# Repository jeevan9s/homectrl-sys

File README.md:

# homectrl

Home-automation controller with a Next.js dashboard. 

 ### Status
>- Controller PCB currently being manufactures
>- Firmware and **docs development** in progress.
>- Mechanical components currently being printed.

<details>
<summary><strong>Table of Contents</strong></summary>

- [homectrl](#homectrl)
    - [Status](#status)
  - [Overview](#overview)
  - [Features](#features)
    - [Controller](#controller)
    - [App](#app)
    - [Mechanical](#mechanical)
  - [Architecture](#architecture)
    - [Systems](#systems)
  - [Electrical](#electrical)
    - [Power System](#power-system)
    - [Microcontroller](#microcontroller)
    - [Pump Interface](#pump-interface)
    - [Stepper Motor Interface](#stepper-motor-interface)
    - [Peripheral Devices](#peripheral-devices)
  - [Mechanical](#mechanical-1)
    - [Container](#container)
    - [Lid](#lid)
  - [Firmware](#firmware)
  - [Web-App](#web-app)
  - [Repository Structure](#repository-structure)
  - [Gallery](#gallery)

</details>

I built homectrl because I wanted to automate my first apartment. 

<table> 
  <tr> 
    <td width="50%"> 
       
    </td> 
    <td width="50%"> 
       
    </td> 
  </tr> 
</table>

## Overview
Practicality is a consistent motive when building. 

As I moved into my first apartment during my first year at Queen's University, I wanted a device capable of smart-control for plants and window blinds, which are main components of my studio. This pushed me to build **homectrl**, a controller that leverages sensor readings, actuators, and WiFi for home automation. 

The first version was manufactured in October of 2025, and this was my first PCB designed. It was a bit elementary, lots of breakout boards soldered on, an MCU devkit, etc. 
Over the year I designed several other PCBs and learned a lot, which pushed me to produce a second version that I can use reliably for my 2nd year in Kingston. 

It's now June and the controller is being manufactured while I write docs and firmware. 

## Features 
### Controller

The controller is powered by a 12V 2A adapter and driven by an ESP32-S3.

Below is a list of features from power circuits to various peripherals. 
- Power-entry circuitry with OC/OV protetction, RPP, and PI-filter
- Regulation circuit featuring buck converter, 5V ORing, and LDO for logic power (3V3) 
- ESP32-S3 breakout circuitry with USB differential routing, S3 boot mode selection and reset toggle. 
- Controlled power delivery via CMOS and PMOS for main pump and moisture sensor power. 
- Low-side switching for pump control. 
- Stepper motor driven by TMC2209 with UART for blind control. 
- Float switches for monitoring irrigation tank. 
- Analog soil moisture sensor connectors with local RC filters. 
- ESD protection with TVS diode arrays on all external connections. 
- Visual and audible indication. 

### App

The controller communicates to a Next.js webapp via Websockets and is also connected to Alexa via SinricPro for voice control, over WiFi/MQTT.

- Next.js dashboard with modern responsive shadCN-tailwindcss UI. 
- Slider and switch control via UI. 
- Voice control with Alexa via SinricPro

### Mechanical 
- Lightweight container with USB and power ports and slots for cable management.
- Vents for airflow and audible indication. 
- Magnetic joints for easy lid removal and secure operation. 

## Architecture 
### Systems 

## Electrical 

This section provides low-level explanations of the significant circuits of each "module" of the controller.

I encourage you to clone the repo or you use [KiCanvas](https://kicanvas.org/) to look at the schematic and board files. 

All electronics were designed with **KiCad**.

### Power System

**Power Entry**

The 12V 2A power enters through a barrel jack connector, where it is then met with a 24V 3A fuse for over-current protection. A PTC resettable fuse was selected for durability. 

The positive plug line `VPLUG` is then protected from voltage spikes with a Transient Voltage Supression (TVS) diode placed in paralell for clamping. 
- The diode's standoff @ `14V`
- Breakdown @ `15.3V`
- Clamps @ `23.2V`

The positive line then goes through a Reverse Polarity Protection (RPP) circuit, using a P-Channel MOSFET for lossless efficiency (lower V drop than standard diodes). 

A Zener diode and resistor is placed between the MOSFET's gate and source for gate over-voltage protection. 

A bulk electrolytic (100μF) capacitor, ferrite bead, and high-frequency (0.1μF) capacitor are then placed to create a third-order low pass filter (π-filter). 
- This is used to smooth voltage spikes and reduce EMI.

The ferrite bead was primariy selected for its saturation current and DCR. 

The approximate current draw with safety margin $I_{net}$ is 2A.

$I_{\mathrm{sat}} = 1.5 \times I_{\mathrm{net}} \approx 3 A$

Minimize heat dissipation. 

$DCR$ is 20Ω

$P_{heat} = DCR \times I_{\mathrm{sat}} \approx 0.06 W$

**Voltage Regulation (I)**

The controller uses a cascade regulation system, starting with the `TPS5405DR` buck converter. 

The input voltage is `VPLUG` (12V), after the protection and filtering circuitry, and the output is 5V. 

The $R_{osc}$ value will determine the switching frequency of the converter. 

Switching frequency is governed by the relationship. 
$$R_{\text{OSC}} (\text{k}\Omega) = 21.82 \cdot f_{\text{SW}}^{-1.167}$$

I chose a value of `50kΩ` for a $f_{SW}$ of approximately `525 kHz`

For the soft-start capacitor $C_{ss}$ , I chose a value of `10nF` for a soft-start time of `5ms`

The values below were taken from the [TPS5405DR Datasheet](https://www.ti.com/lit/gpn/tps5405)

$$
C_{SS} = \frac{t_{SS} \cdot I_{SS}}{V_{REF}}
$$

$$
C_{SS} = \frac{(5\,\mathrm{ms})(2\,\mathrm{\mu A})}{0.8\,\mathrm{V}}
= 12.5\,\mathrm{nF}
\approx 10\,\mathrm{nF}
$$

The inductor values were chosen using the equation below. 

$$
L=\frac{V_{out}\left(V_{in}-V_{out}\right)}
{V_{in}f_{sw}\Delta I_L}
$$

Using our calculated $f_{sw}$ from above and our voltage requirements (12V in, 5V out):
$$
L=
\frac{(5\,\mathrm{V})(12\,\mathrm{V}-5\,\mathrm{V})}
{(12\,\mathrm{V})(490\,\mathrm{kHz})(0.6\,\mathrm{A})}

\approx
10\,\mathrm{\mu H}
$$

The Schottky diode is rated for the `2A` output current and `12V`

**5V ORing**

The `5V` rails from both USB and the buck converter are combined using an OR-ing circuit (Dual Ideal Diodes) to prevent backfeeding before feeding the second stage of regulation.

In this configuration, the outputs of both `LM66100` ideal diode controllers are tied together to form the shared `5V` rail. The `CE` pins of each device are also tied to the output rail, ensuring both controllers are only enabled once the rail is present 

This allows for testing over serial with devices that are powered by `VPLUG` (12V). 

**Voltage Regulation (II)**

The second stage of voltage regulation involes a Low-Dropout Regulator (LDO), the `MCP1826S`

It is fed the combined `5V` rail from the OR-ing circuit to produce the controller's logic-level voltage: `3V3`

**Controlled Pump Power Delivery**

The power for the pumps is controlled using a complementary-MOSFET (CMOS) setup, driven by a digital `HIGH` from the S3.

- When the control signal is low or floating, the N-channel MOSFET remains off and a pull-up resistor holds the gate of the P-channel MOSFET at the supply voltage, keeping it disabled and disconnecting the load rail.
- When the control signal is driven high, the N-channel MOSFET turns on and pulls the P-channel gate low, creating sufficient gate-source voltage to enable conduction and connect the supply to the load.

**Voltage Sensing**

A resistor divider circuit is used to produce a signal to be read by the S3's internal ADC.

- $R_1 = 100\,\mathrm{k\Omega}$
- $V_{plug} = 12\,\mathrm{V}$
- $V_{out} = 2\,\mathrm{V}$

$$
R_2 = \frac{R_1 \cdot V_{out}}{V_{batt} - V_{out}}
$$

$$
R_2 = \frac{100\,000 \cdot 2}{12 - 2}
= 20\,\mathrm{k\Omega}
$$

### Microcontroller
The controller is driven by an ESP32-S3-WROOM microcontroller.

**Digital IO**

**Mode Select and Reset Toggle**

The S3 can be put into **BOOT** mode and **RESET** with onboard buttons.

**BOOT** mode determines whether the chip runs existing code from flash memory or waits to download new firmware.
- The ESP32 samples the **BOOT** pin (`GPIO0`) during reset to determine the boot mode.
- It is **active-low**: when pulled to **GND** during reset, the chip enters UART bootloader mode for flashing firmware.
- The circuit uses a momentary push-button to **GND** and a `10kΩ` pull-up resistor to ensure a defined high state during normal operation.

| BOOT0 Level | Boot Mode |
|-------------|-----------|
| HIGH | Programming Mode |
| LOW | Memory Mode |

**RESET** controls the Enable (EN) pin which is the ON/OFF (reset) switch for the ESP32.
- It is **active-low**: when pulled to **GND** it turns off the chip, and when released, it restarts.
- The circuit consists of a momentary push-button, a pull-up resistor to ensure the chip is enabled by default, and a `1µF` capacitor to filter out button noise.

### Pump Interface

<table><tr><td width="50%"></td><td width="50%"></td></tr></table>

The controller interfaces with 12V 300mA rated pumps for irrigation. 

These pumps connect via JST-XH vertical headers and are met with flyback diodes for inductive spike protection, and decoupling to filter out noise. 

Each pump is controlled by a low-side switch using an `A03400A` N-channel MOSFET. 
- The gate of the MOSFET is driven by an S3 GPIO pin and is pulled down to GND for state definition. 
- The drain is connected to the negative terminal of the pump and the source to GND. 

This will bridge the negative pump terminal to GND and effectively turn it `ON` when the gate is `HIGH`. 

### Stepper Motor Interface

The controller interfaces with a `NEMA 17` stepper motor through a `TMC2209` driver for blind control. 

The `NEMA 17` stepper motor connects via a vertical 4-position JST-XH header. 

The positive and negative terminals of both stepper coils feed the OBX and OAX pins of the driver. 

The driver is powered by `VPLUG` and is decoupled for bulk and high-frequency noise with electrolytic and ceramic capacitors. 
- The driver is put to sleep by the `ENN` pin to avoid power consumption, which is why I didn't use a CMOS/controlled-power delivery setup.

The main control signals are `STEP` and `DIR`, controlling the speed and direction, respectively. These connect digital pins on the S3. 

The single-wire UART interface was used for advanced chip config, live diagnostics, and features. 

The `BRA` and `BRB` connect to `0.11Ω` sense resistors to monitor and regulate current through the motor coils. 

For addressing, the `MS1_AD01` and `MS2_AD1` pins are pulled low to set the binary address bits to `00` and the UART slave address to `%0`. 

The `CP0` and `CP1` pins are tied together with a 22nF capacitor to generate a boost voltage for the internal charge pump. This boosted voltage switches the internal N-channel MOSFETs fully on. 

### Peripheral Devices

**Sensors**

The controller interfaces with two capactive soil-moisture sensors (SMS) and an Ambient Light Sensor (ALS). 

These connections are made with vertical 4-pin JST-XH headers. 

I designed the ALS breakout board, in the future I'd be interested in designing the moisture sensors. For now I'm using the Adafruit models.

The `3V3` SMS power  is controlled through a simple `A03407A` P-channel mosfet, and the signals are filtered with a resistor-capacitor network at the S3 ADC pins. 

The ALS communicates with the `I2C` protocol and is powered by `3V3`. 

The two analog signals and I2C clock and data signals are ESD-protected by a `TPD43001` TVS diode array.

**Float Switches**

The controller interfaces with two float switches. 

These connections are made with a vertical 3-pin JST-XH header. 

The signals are pulled up to 3V3 to establish a defined logic stateand filtered with a resistor-capacitor network at the S3 ADC pins. 

**Indicator Components**
- RGB LED
- Passive LEDs for simple indication
- Buzzer for audible indication

## Mechanical 
This section provides insight on the mechanical components of homectrl. 

I used Fusion360 to design everything.   

### Container

The container uses a rounded-rectangular exterior to house the board. 

The board is mounted using M2 standoffs designed from the base of the container. 

- It features USB-C and barrel-jack portholes for easy flashing and power connection.
- The backside has slot cutouts for actuator and sensor cables. 
- Vent holes were used throughout the container for airflow and weight management (more lightweight).

### Lid 

The lid is mounted magnetically on the outer top face of the container using projected holes for small magnets. 
- Its design is honestly quite minimal, I did add a small hole for the controller's RGB LED to shine through. 

## Firmware

## Web-App

## Repository Structure 

## Gallery 

---
**huge thanks to PCBWay for sponsoring this project's first revision.**<br>
[check out **REV A**](https://github.com/jeevan9s/homectrl-sys/tree/rev-A)

---
Jeevan Sanchez, 2026

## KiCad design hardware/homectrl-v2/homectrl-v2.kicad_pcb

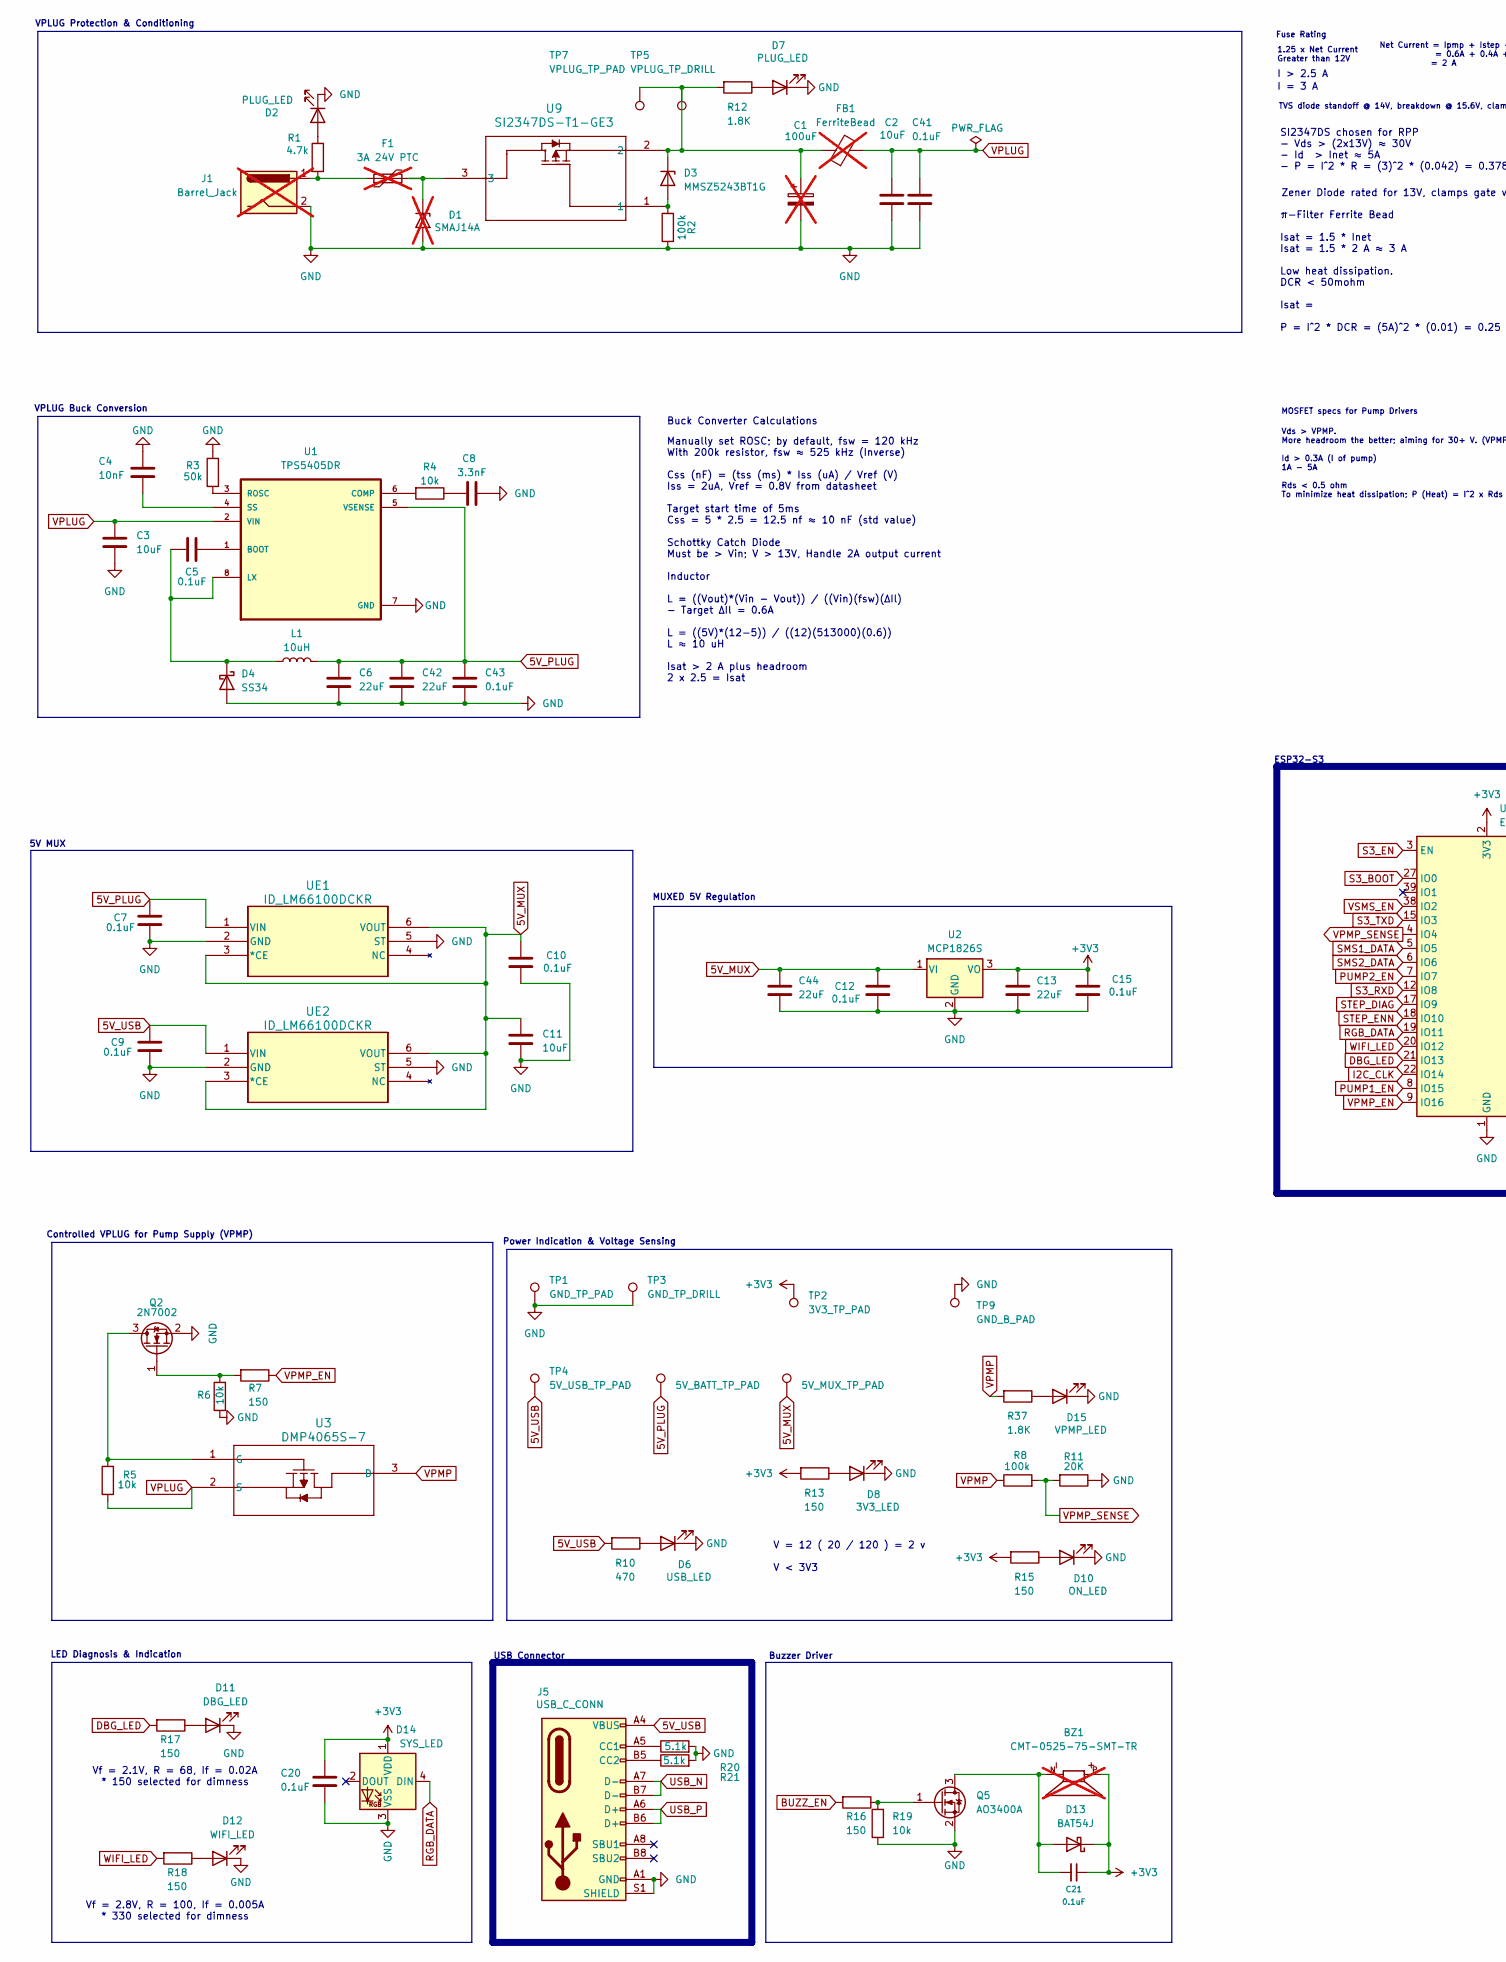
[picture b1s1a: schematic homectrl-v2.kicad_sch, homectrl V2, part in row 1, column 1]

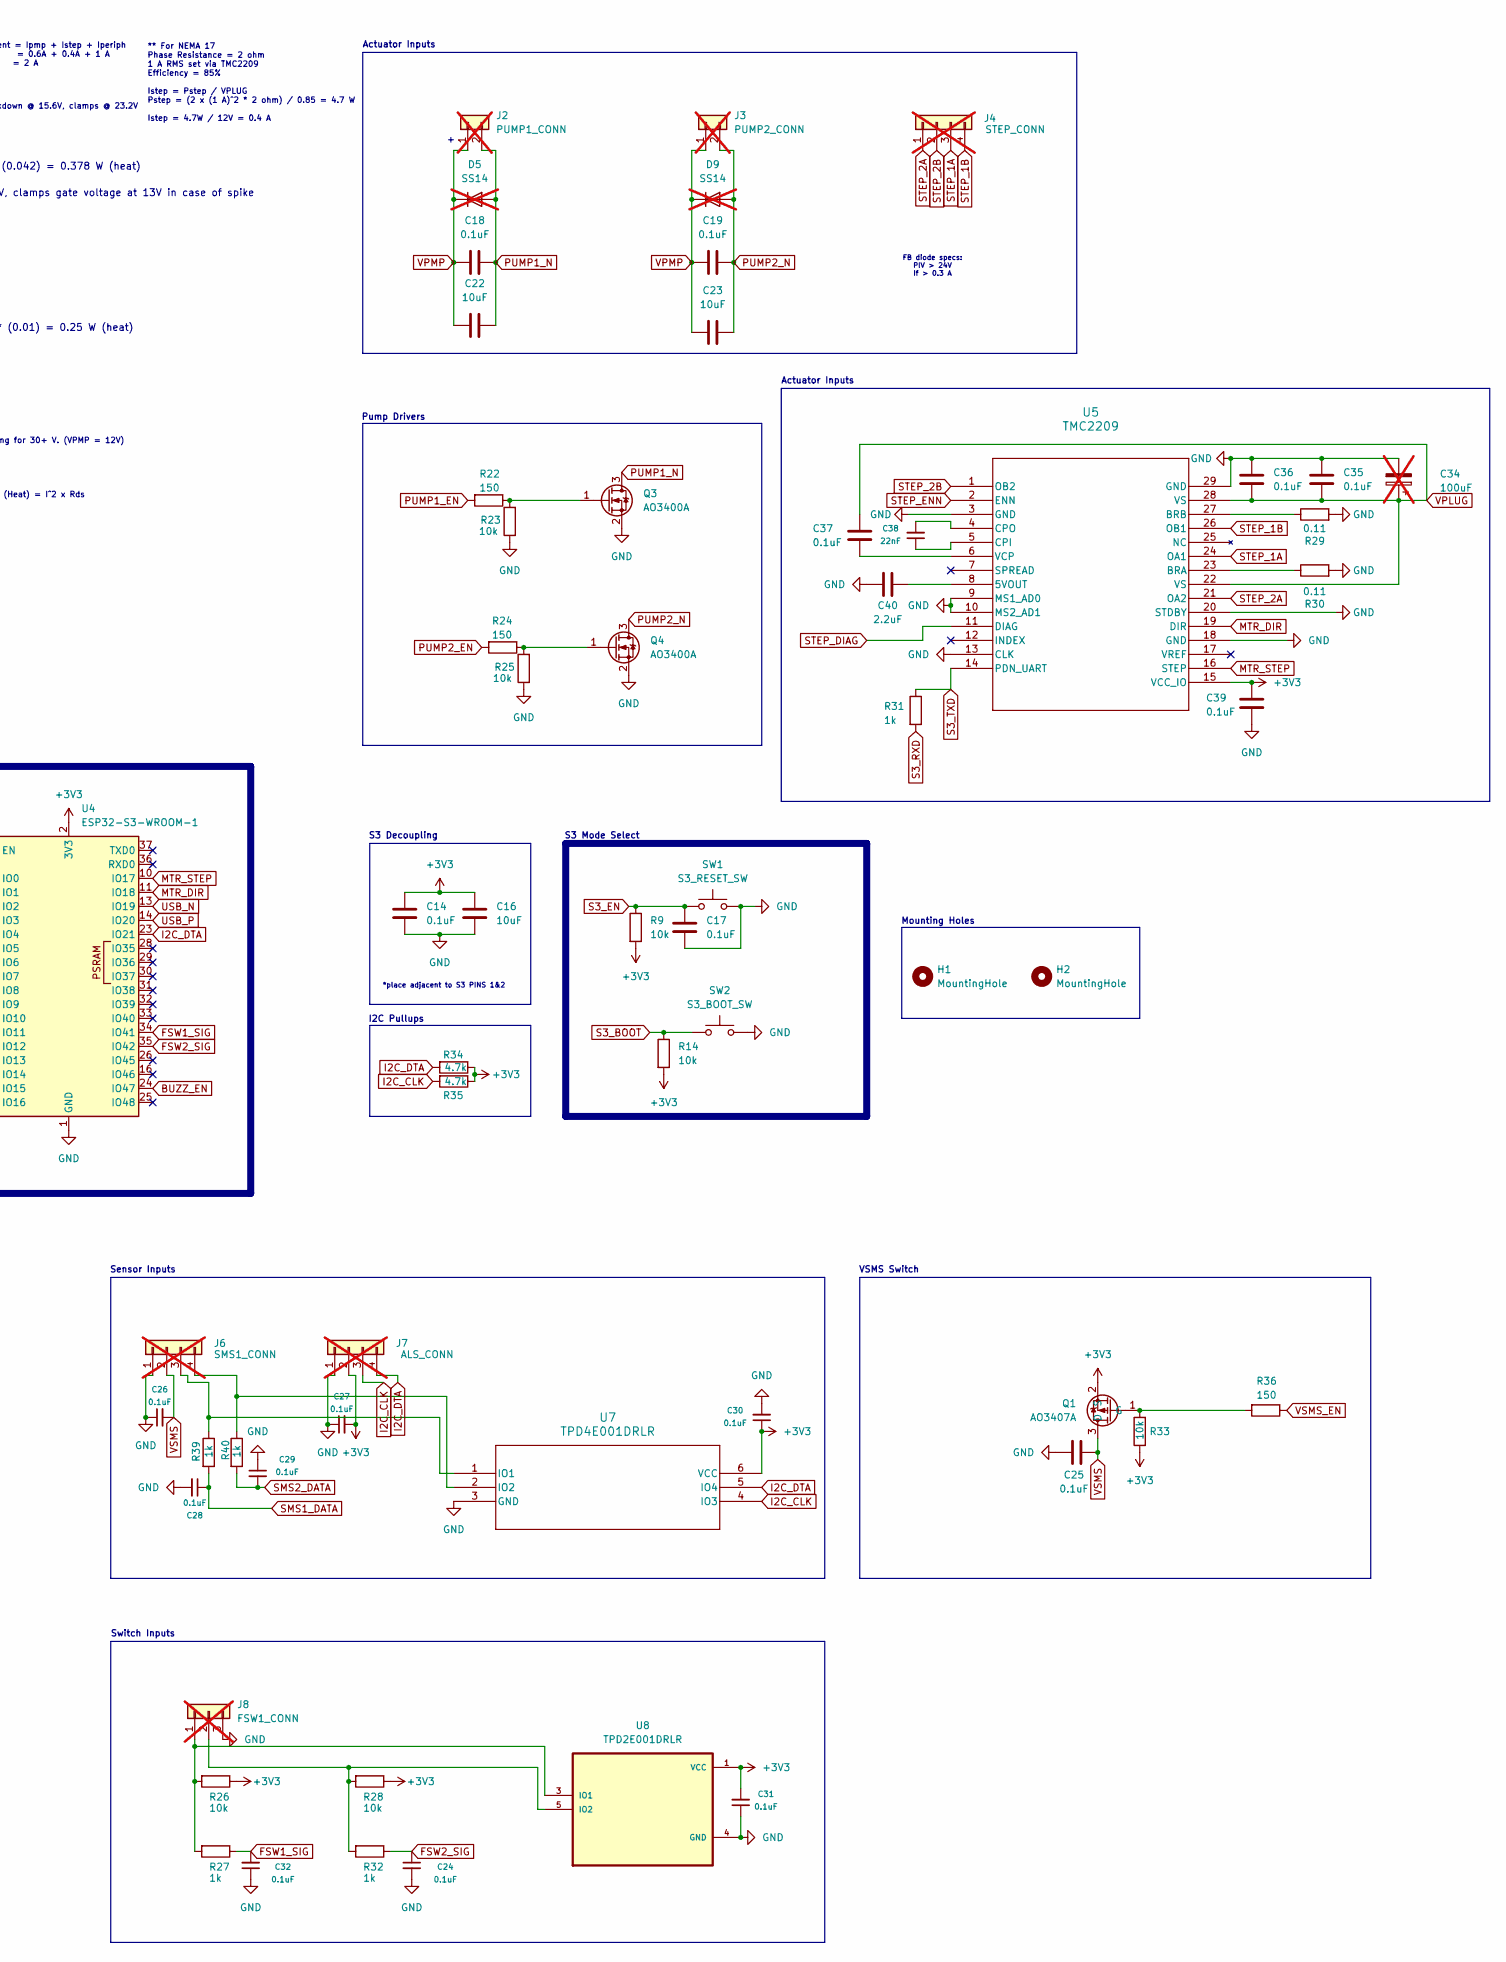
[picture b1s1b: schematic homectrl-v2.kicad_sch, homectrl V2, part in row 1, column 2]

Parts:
BZ1: CMT-0525-75-SMT-TR; XDCR_CMT-0525-75-SMT-TR; PARTREV 1.0; not fitted
C1: 100uF; CAP_EEHZK1V101XP; MPN EEE-FK1V101P; not fitted
C2: 10uF; C_0805_2012Metric; MPN CL21A106KAYNNNE; LCSC C15850
C3: 10uF; C_0805_2012Metric; LCSC C15850
C4: 10nF; C_0402_1005Metric; LCSC C15195
C5, C7, C9, C10, C12, C14, C15, C17, C20, C21, C24, C25, C26, C27, C28, C29, C30, C31, C32, C35, C36, C37, C39, C41, C43: 0.1uF; C_0402_1005Metric; LCSC C77020
C6, C42: 22uF; C_0805_2012Metric; LCSC C45783
C8: 3.3nF; C_0402_1005Metric; LCSC C26404
C11, C16, C22, C23: 10uF; C_0603_1608Metric; LCSC C96446
C13, C44: 22uF; C_0805_2012Metric; LCSC C49326779
C18, C19: 0.1uF; C_0603_1608Metric; LCSC C14663
C34: 100uF; CAP_EEHZK1V101XP; not fitted
C38: 22nF; C_0402_1005Metric; LCSC C1532
C40: 2.2uF; C_0402_1005Metric; LCSC C72203
D1: SMAJ14A; D_SMA; not fitted
D2: PLUG_LED; LED_0603_1608Metric; LCSC C2297
D3: MMSZ5243BT1G; D_SOD-123; LCSC C2856864
D4: SS34; Nexperia_CFP3_SOD-123W; LCSC C5380710
D5, D9: SS14; D_SMA; not fitted
D6: USB_LED; LED_0603_1608Metric; LCSC C2297
D7: PLUG_LED; LED_0603_1608Metric; LCSC C12065
D8: 3V3_LED; LED_0603_1608Metric; LCSC C12065
D10: ON_LED; LED_0603_1608Metric; LCSC C2297
D11: DBG_LED; LED_0603_1608Metric; LCSC C72038
D12: WIFI_LED; LED_0603_1608Metric; LCSC C72041
D13: BAT54J; D_SOD-323F; LCSC C86299
D14: SYS_LED; LED_WS2812B-Mini_PLCC4_3.5x3.5mm; Digikey 1568-COM-16347CT-ND
D15: VPMP_LED; LED_0603_1608Metric; LCSC C12065
F1: 3A 24V PTC; Fuse_1812_4532Metric; not fitted
FB1: FerriteBead; R_1206_3216Metric; not fitted
H1, H2: MountingHole; MountingHole_2.2mm_M2
J1: Barrel_Jack; BarrelJack_Horizontal; not fitted
J2: PUMP1_CONN; JST_XH_B2B-XH-A_1x02_P2.50mm_Vertical; not fitted
J3: PUMP2_CONN; JST_XH_B2B-XH-A_1x02_P2.50mm_Vertical; not fitted
J4: STEP_CONN; JST_XH_B4B-XH-A_1x04_P2.50mm_Vertical; not fitted
J5: USB_C_CONN; USB_C_Receptacle_G-Switch_GT-USB-7010ASV; LCSC C5178541
J6: SMS1_CONN; JST_XH_B4B-XH-A_1x04_P2.50mm_Vertical; not fitted
J7: ALS_CONN; JST_XH_B4B-XH-A_1x04_P2.50mm_Vertical; not fitted
J8: FSW1_CONN; JST_XH_B3B-XH-A_1x03_P2.50mm_Vertical; not fitted
L1: 10uH; L_Changjiang_FNR6045S; LCSC C360734
Q1: AO3407A; SOT-23; LCSC C15155
Q2: 2N7002; SOT-23; LCSC C8545
Q3, Q4, Q5: AO3400A; SOT-23; LCSC C20917
R1, R34, R35: 4.7k; R_0402_1005Metric; LCSC C22765
R2: 100k; R_0603_1608Metric; LCSC C1996
R3: 50k; R_0402_1005Metric; LCSC C166559
R4, R5, R6, R9, R14, R19, R23, R25, R26, R28, R33: 10k; R_0402_1005Metric; LCSC C25744
R7, R13, R15, R16, R17, R18, R22, R24, R36: 150; R_0402_1005Metric; LCSC C25082
R8: 100k; R_0402_1005Metric; LCSC C25741
R10: 470; R_0402_1005Metric; LCSC C174152
R11: 20K; R_0402_1005Metric; LCSC C22356231
R12, R37: 1.8K; R_0402_1005Metric; LCSC C174229
R20, R21: 5.1k; R_0402_1005Metric; LCSC C25905
R27, R31, R32, R39, R40: 1k; R_0402_1005Metric; LCSC C11702
R29, R30: 0.11; R_0603_1608Metric; LCSC C247140
SW1: S3_RESET_SW; SW_5-B-B-B-A_XKB; LCSC C561521
SW2: S3_BOOT_SW; SW_5-B-B-B-A_XKB; LCSC C561521
TP1: GND_TP_PAD; TestPoint_Pad_1.5x1.5mm
TP2: 3V3_TP_PAD; TestPoint_Pad_1.5x1.5mm
TP3: GND_TP_DRILL; TestPoint_THTPad_D1.0mm_Drill0.5mm
TP4: 5V_USB_TP_PAD; TestPoint_Pad_1.0x1.0mm
TP5: VPLUG_TP_DRILL; TestPoint_THTPad_D1.0mm_Drill0.5mm
TP6: 5V_BATT_TP_PAD; TestPoint_Pad_1.0x1.0mm
TP7: VPLUG_TP_PAD; TestPoint_Pad_1.0x1.0mm
TP8: 5V_MUX_TP_PAD; TestPoint_Pad_1.0x1.0mm
TP9: GND_B_PAD; TestPoint_Pad_1.0x1.0mm
U1: TPS5405DR; SOIC127P599X175-8N; LCSC C488409
U2: MCP1826S; SOT-223-3_TabPin2; LCSC C638624
U3: DMP4065S-7; SOT-23; LCSC C182476
U4: ESP32-S3-WROOM-1; XCVR_ESP32-S3-WROOM-1-N16R2; LCSC C2913199
U5: TMC2209; QFN28_5X5_TRI; LCSC C2150710
U7: TPD4E001DRLR; Texas_R-PDSO-N6_DRL-6; LCSC C527516
U8: TPD2E001DRLR; SOT50P160X60-5N; DigiKey_Part_Number 296-21883-1-ND
U9: SI2347DS-T1-GE3; SOT_7DS-T1-GE3_VIS; LCSC C145002
UE1, UE2: ID_LM66100DCKR; SOT-363_SC-70-6; LCSC C2869734

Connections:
5V_MUX: C10.2, C11.2, C12.2, C44.1, TP8.1, U2.1 (VI), UE1.3 (*CE), UE1.6 (VOUT), UE2.3 (*CE), UE2.6 (VOUT)
5V_PLUG: C6.1, C7.2, C42.1, C43.1, L1.2, TP6.1, U1.5 (VSENSE), UE1.1 (VIN)
5V_USB: C9.1, J5.A4 (VBUS), J5.A9 (VBUS), J5.B4 (VBUS), J5.B9 (VBUS), R10.2, TP4.1, UE2.1 (VIN)
+3V3: BZ1.P, C13.1, C14.1, C15.2, C16.1, C20.1, C21.1, C27.2, C30.1, C31.2, C39.1, D13.1 (K), D14.1 (VDD), J7.2, Q1.2 (S), R9.2, R13.2, R14.2, R15.2, R26.1, R28.1, R33.1, R34.1, R35.1, TP2.1, U2.3 (VO), U4.2 (3V3), U5.15 (VCC_IO), U7.6 (VCC), U8.1 (VCC)
BUZZ_EN: R16.2, U4.24 (IO47)
DBG_LED: R17.2, U4.21 (IO13)
FSW1_SIG: C32.2, R27.1, U4.34 (IO41)
FSW2_SIG: C24.1, R32.1, U4.35 (IO42)
GND: C1.2, C2.1, C3.2, C4.1, C6.2, C7.1, C8.2, C9.2, C10.1, C11.1, C12.1, C13.2, C14.2, C15.1, C16.2, C17.2, C20.2, C24.2, C25.2, C26.1, C27.1, C28.2, C29.1, C30.2, C31.1, C32.1, C34.2, C35.1, C36.1, C39.2, C40.1, C41.2, C42.2, C43.2, C44.2, D1.2 (A2), D2.1 (K), D4.2 (A), D6.1 (K), D7.1 (K), D8.1 (K), D10.1 (K), D11.1 (K), D12.1 (K), D14.3 (VSS), D15.1 (K), J1.2, J5.A1 (GND), J5.A12 (GND), J5.B1 (GND), J5.B12 (GND), J5.S1 (SHIELD), J6.1, J7.1, J8.3, Q2.2 (S), Q3.2 (S), Q4.2 (S), Q5.2 (S), R2.1, R3.2, R6.1, R11.1, R19.1, R20.2, R21.2, R23.1, R25.1, R29.2, R30.2, SW1.2, SW2.2, TP1.1, TP3.1, TP9.1, U1.7 (GND), U2.2 (GND), U4.1 (GND), U4.40 (GND), U4.41 (GND), U5.3 (GND), U5.9 (MS1_AD0), U5.10 (MS2_AD1), U5.13 (CLK), U5.18 (GND), U5.20 (STDBY), U5.29 (GND), U7.3 (GND), U8.4 (GND), UE1.2 (GND), UE1.5 (ST), UE2.2 (GND), UE2.5 (ST)
I2C_CLK: J7.3, R35.2, U4.22 (IO14), U7.4 (IO3)
I2C_DTA: J7.4, R34.2, U4.23 (IO21), U7.5 (IO4)
MTR_DIR: U4.11 (IO18), U5.19 (DIR)
MTR_STEP: U4.10 (IO17), U5.16 (STEP)
unnamed: C8.1, R4.1
unnamed: D1.1 (A1), F1.2, U9.3
unnamed: D2.2 (A), R1.1
unnamed: D3.2 (A), R2.2, U9.1
unnamed: C1.1, D3.1 (K), FB1.1, R12.2, TP5.1, TP7.1, U9.2
unnamed: C5.1, D4.1 (K), L1.1, U1.8 (LX)
unnamed: D6.2 (A), R10.1
unnamed: D7.2 (A), R12.1
unnamed: D8.2 (A), R13.1
unnamed: D10.2 (A), R15.1
unnamed: D11.2 (A), R17.1
unnamed: D12.2 (A), R18.1
unnamed: BZ1.N, C21.2, D13.2 (A), Q5.3 (D)
unnamed: D15.2 (A), R37.1
unnamed: F1.1, J1.1, R1.2
unnamed: J5.A5 (CC1), R20.1
unnamed: J5.B5 (CC2), R21.1
unnamed: J6.3, R39.1, U7.1 (IO1)
unnamed: J6.4, R40.1, U7.2 (IO2)
unnamed: J8.1, R26.2, R27.2, U8.3 (IO1)
unnamed: J8.2, R28.2, R32.2, U8.5 (IO2)
unnamed: Q1.1 (G), R33.2, R36.2
unnamed: Q2.3 (D), R5.2, U3.1 (G)
unnamed: Q2.1 (G), R6.2, R7.2
unnamed: Q3.1 (G), R22.1, R23.2
unnamed: Q4.1 (G), R24.1, R25.2
unnamed: Q5.1 (G), R16.1, R19.2
unnamed: C5.2, U1.1 (BOOT)
unnamed: R4.2, U1.6 (COMP)
unnamed: R3.1, U1.3 (ROSC)
unnamed: C4.2, U1.4 (SS)
unnamed: C40.2, U5.8 (5VOUT)
unnamed: R30.1, U5.23 (BRA)
unnamed: R29.1, U5.27 (BRB)
unnamed: C38.1, U5.5 (CPI)
unnamed: C38.2, U5.4 (CPO)
unnamed: C37.2, U5.6 (VCP)
PUMP1_EN: R22.2, U4.8 (IO15)
PUMP1_N: C18.2, C22.2, D5.2 (A), J2.2, Q3.3 (D)
PUMP2_EN: R24.2, U4.7 (IO7)
PUMP2_N: C19.2, C23.2, D9.2 (A), J3.2, Q4.3 (D)
RGB_DATA: D14.4 (DIN), U4.19 (IO11)
S3_BOOT: R14.1, SW2.1, U4.27 (IO0)
S3_EN: C17.1, R9.1, SW1.1, U4.3 (EN)
S3_RXD: R31.2, U4.12 (IO8)
S3_TXD: R31.1, U4.15 (IO3), U5.14 (PDN_UART)
SMS1_DATA: C28.1, R39.2, U4.5 (IO5)
SMS2_DATA: C29.2, R40.2, U4.6 (IO6)
STEP_1A: J4.3, U5.24 (OA1)
STEP_1B: J4.4, U5.26 (OB1)
STEP_2A: J4.1, U5.21 (OA2)
STEP_2B: J4.2, U5.1 (OB2)
STEP_DIAG: U4.17 (IO9), U5.11 (DIAG)
STEP_ENN: U4.18 (IO10), U5.2 (ENN)
USB_N: J5.A7 (D-), J5.B7 (D-), U4.13 (IO19)
USB_P: J5.A6 (D+), J5.B6 (D+), U4.14 (IO20)
VPLUG: C2.2, C3.1, C34.1, C35.2, C36.2, C37.1, C41.1, FB1.2, R5.1, U1.2 (VIN), U3.2 (S), U5.22 (VS), U5.28 (VS)
VPMP: C18.1, C19.1, C22.1, C23.1, D5.1 (K), D9.1 (K), J2.1, J3.1, R8.1, R37.2, U3.3 (D)
VPMP_EN: R7.1, U4.9 (IO16)
VPMP_SENSE: R8.2, R11.2, U4.4 (IO4)
VSMS: C25.1, C26.2, J6.2, Q1.3 (D)
VSMS_EN: R36.1, U4.38 (IO2)
WIFI_LED: R18.2, U4.20 (IO12)

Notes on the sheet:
TVS diode standoff @ 14V, breakdown @ 15.6V, clamps @ 23.2V
Pump Drivers
S3 Decoupling
VPLUG Buck Conversion
Buck Converter Calculations
VPLUG Protection & Conditioning
π-Filter Ferrite Bead Isat = 1.5 * Inet Isat = 1.5 * 2 A ≈ 3 A Low heat dissipation. DCR < 50mohm Isat = P = I^2 * DCR = (5A)^2 * (0.01) = 0.25 W (heat)
Vf = 2.1V, R = 68, If = 0.02A * 150 selected for dimness
Vds > VPMP. More headroom the better; aiming for 30+ V. (VPMP = 12V) Id > 0.3A (I of pump) 1A - 5A Rds < 0.5 ohm To minimize heat dissipation; P (Heat) = I^2 x Rds
VSMS Switch
MUXED 5V Regulation
Controlled VPLUG for Pump Supply (VPMP)
5V MUX
FB diode specs: PIV > 24V If > 0.3 A
I = 3 A
I > 2.5 A
MOSFET specs for Pump Drivers
Switch Inputs
Vf = 2.8V, R = 100, If = 0.005A * 330 selected for dimness
S3 Mode Select
Mounting Holes
Zener Diode rated for 13V, clamps gate voltage at 13V in case of spike
Net Current = Ipmp + Istep + Iperiph = 0.6A + 0.4A + 1 A = 2 A
Power Indication & Voltage Sensing
ESP32-S3
Fuse Rating
Buzzer Driver
SI2347DS chosen for RPP - Vds > (2x13V) ≈ 30V - Id > Inet ≈ 5A - P = I^2 * R = (3)^2 * (0.042) = 0.378 W (heat)
** For NEMA 17 Phase Resistance = 2 ohm 1 A RMS set via TMC2209 Efficiency = 85% Istep = Pstep / VPLUG Pstep = (2 x (1 A)^2 * 2 ohm) / 0.85 = 4.7 W Istep = 4.7W / 12V = 0.4 A
V = 12 ( 20 / 120 ) = 2 v V < 3V3
Sensor Inputs
1.25 x Net Current Greater than 12V
I2C Pullups
Actuator Inputs
LED Diagnosis & Indication
*place adjacent to S3 PINS 1&2
USB Connector
Manually set ROSC; by default, fsw = 120 kHz With 200k resistor, fsw ≈ 525 kHz (Inverse) Css (nF) = (tss (ms) * Iss (uA) / Vref (V) Iss = 2uA, Vref = 0.8V from datasheet Target start time of 5ms Css = 5 * 2.5 = 12.5 nf ≈ 10 nF (std value) Schottky Catch Diode Must be > Vin; V > 13V, Handle 2A outpu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

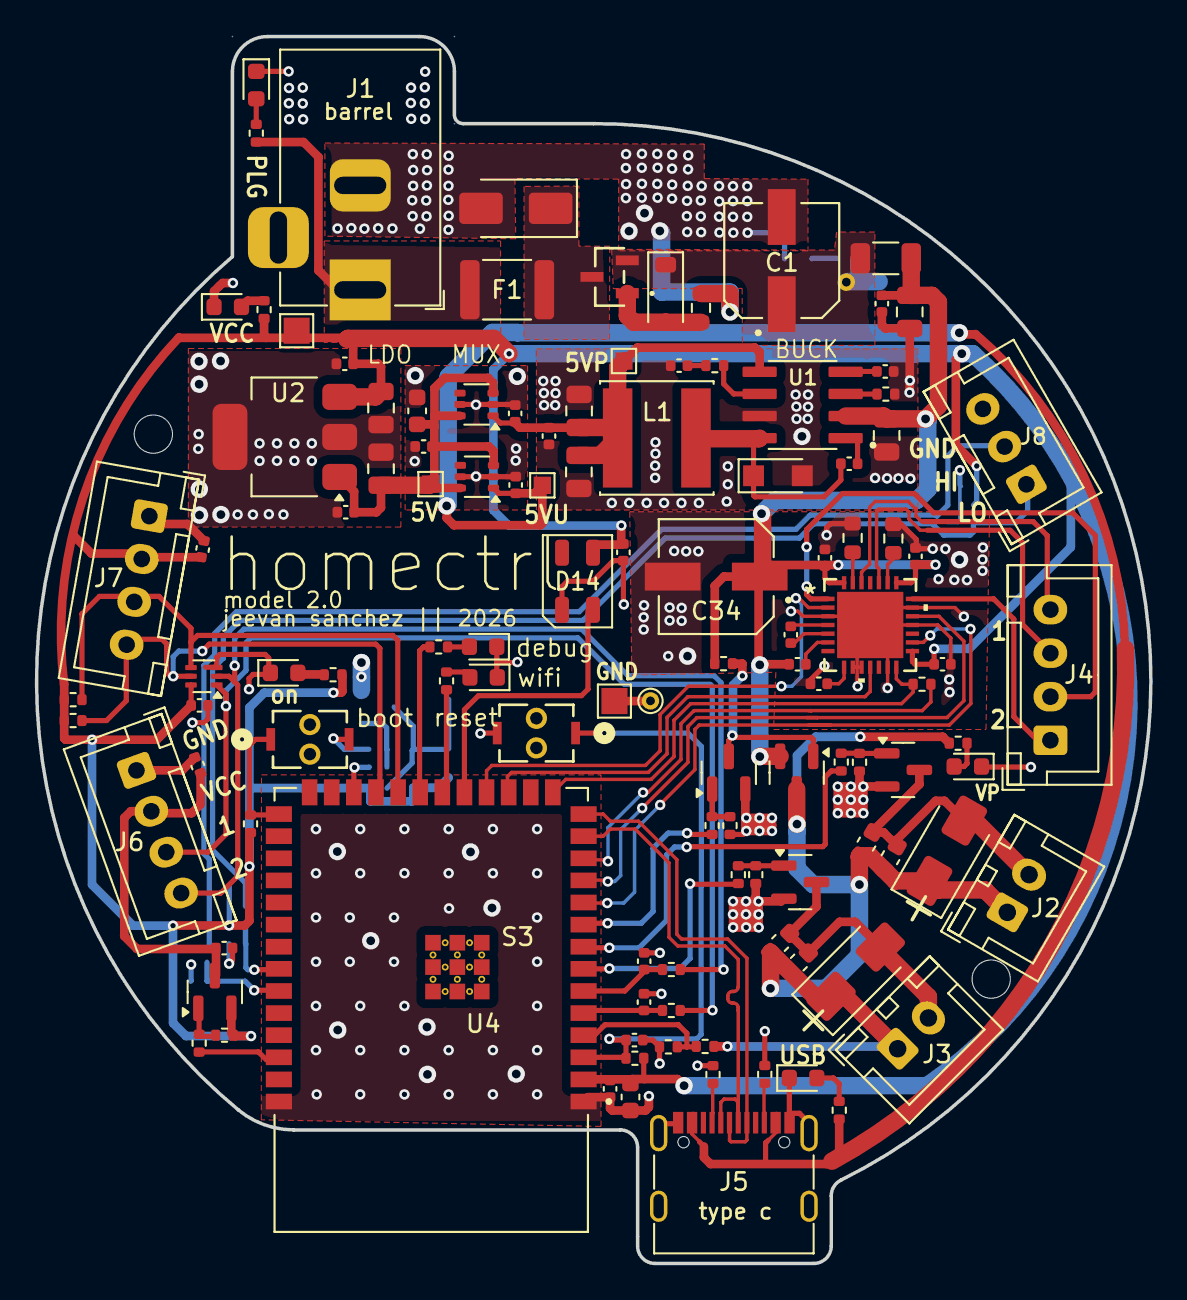
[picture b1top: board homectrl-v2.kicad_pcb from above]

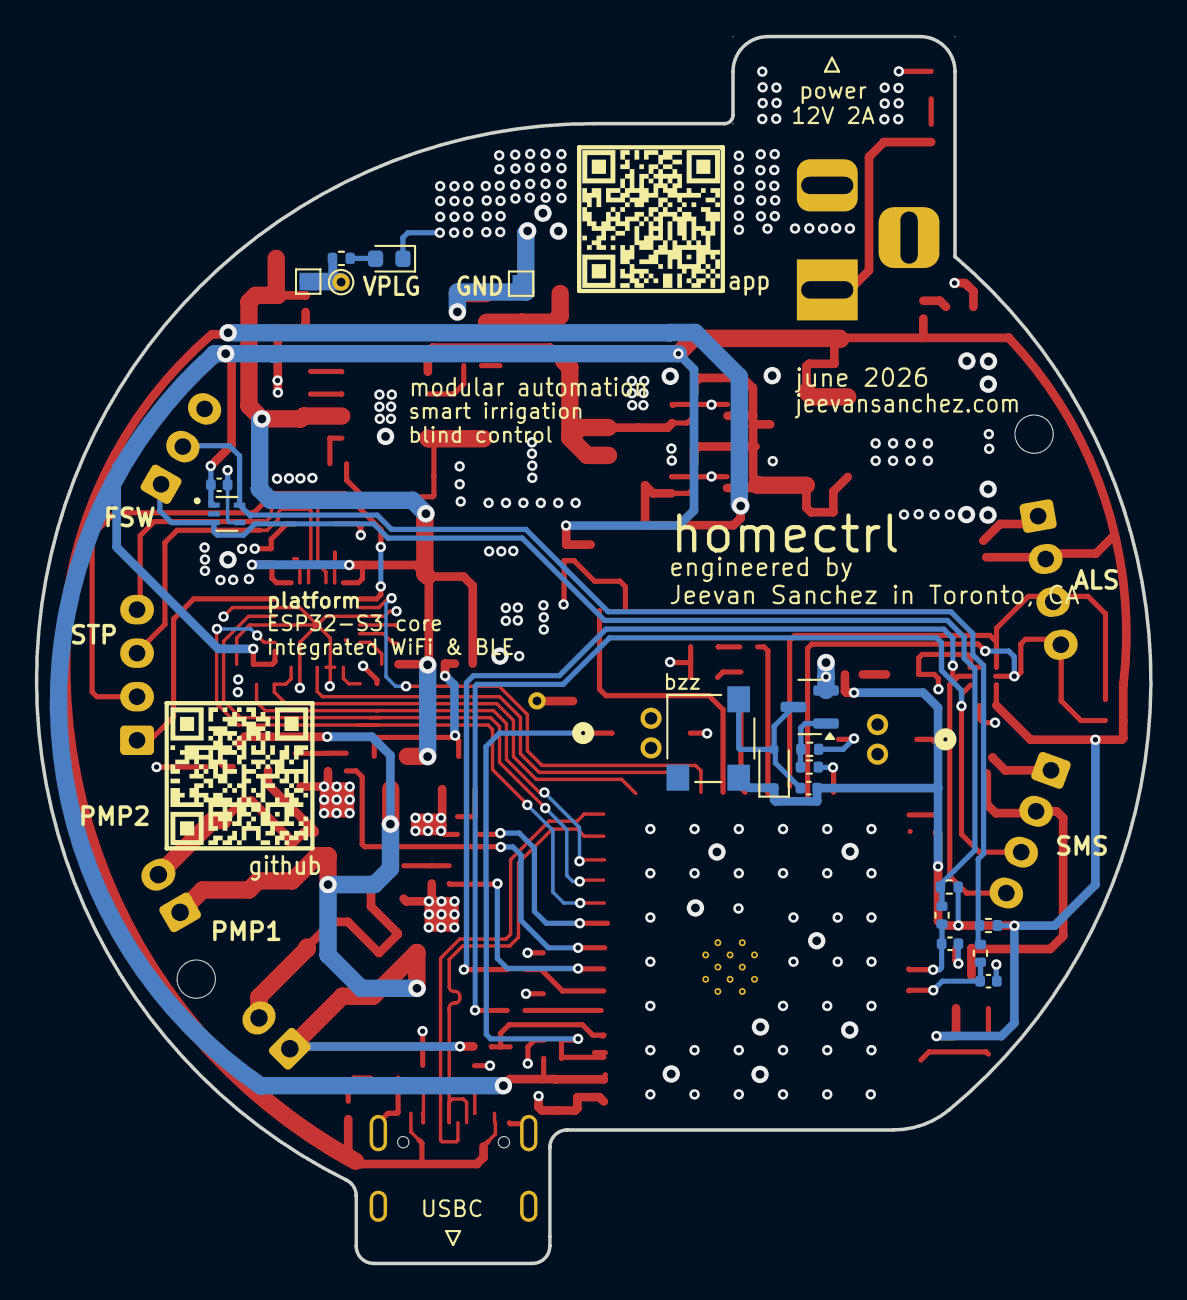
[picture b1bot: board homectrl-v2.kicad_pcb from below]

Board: 4 copper layers, 64.0 x 70.5 mm, 137 parts (19 on the bottom side), 76 nets.

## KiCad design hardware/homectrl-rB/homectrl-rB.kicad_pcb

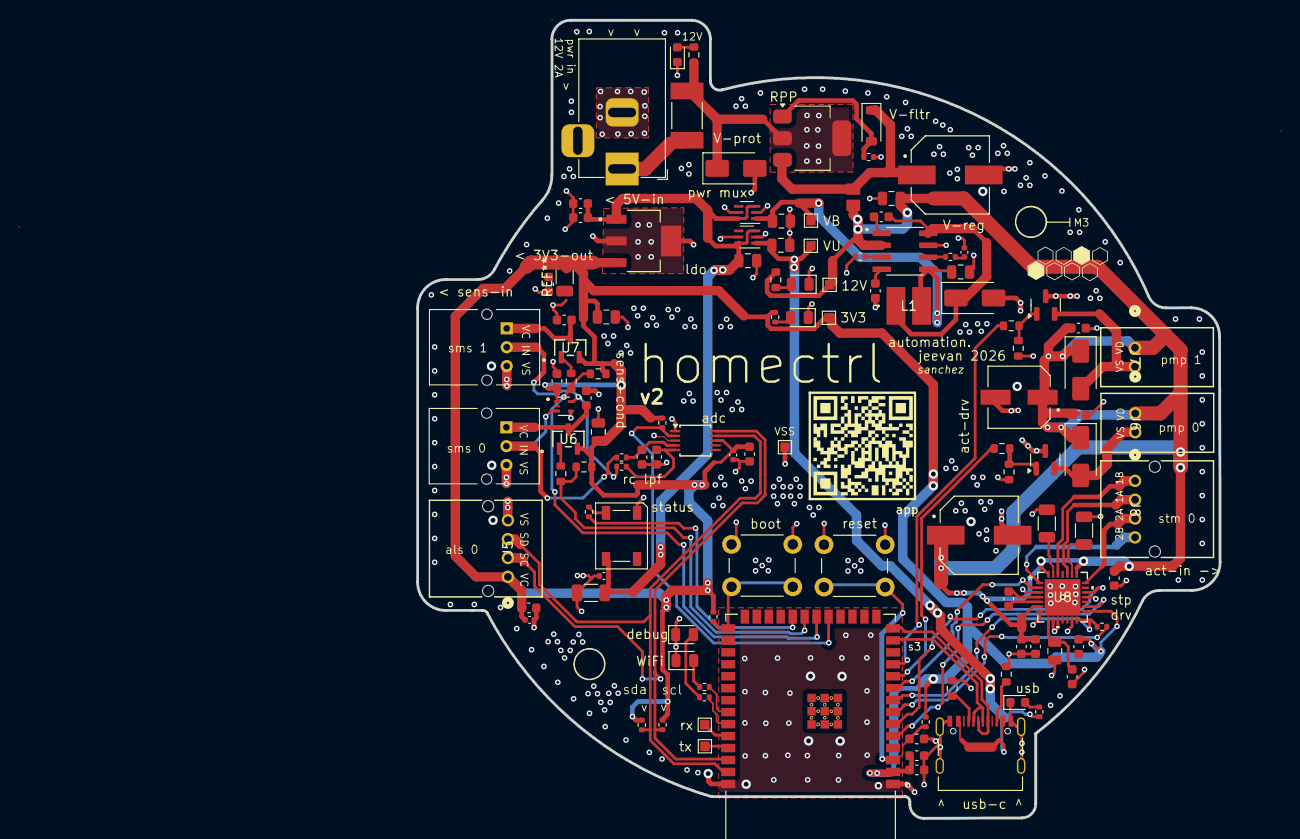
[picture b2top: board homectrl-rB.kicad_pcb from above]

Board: 4 copper layers, 85.2 x 84.7 mm, 116 parts (0 on the bottom side), 67 nets.

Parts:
C1: 100uF; CAP_EEEFK1V101P
C2, C25, C26: 10uF; C_0805_2012Metric
C3: 47 nF; C_0603_1608Metric
C4: 3.3nF; C_0402_1005Metric
C5: 47nF; C_0603_1608Metric
C6, C9: 47uF; C_0805_2012Metric
C7: 0.47uF; C_0603_1608Metric
C10, C16, C17, C19: 10uF; C_0603_1608Metric
C11, C12: 1uF; C_0805_2012Metric
C13, C14, C15, C21, C22, C23, C24, C28, C31, C32, C34, C35, C42, C43: 0.1uF; C_0603_1608Metric
C18, C20, C36: 0.1uF; C_0402_1005Metric
C27: 2.2uF; C_0603_1608Metric
C29: 22nF; C_0603_1608Metric
C30: 4.7uF; C_0805_2012Metric
C33: 220uF; CAP_EEEFK1V101P
C37: 10uF; C_1206_3216Metric
C41: 100uF; CAP_EEHZK1V101XP
D1: SS24; D_SMA
D2: SMAJ15A; D_SMA
D3: D_Zener; D_SOD-123
D4: 12V-LED; LED_0805_2012Metric
D5: 3V3-LED; LED_0805_2012Metric
D6: BUCK-LED; LED_0603_1608Metric
D7: SYS-LED; LED_WS2812B_PLCC4_5.0x5.0mm_P3.2mm
D8: WIFI-LED; LED_0805_2012Metric
D9: DEBUG-LED; LED_0805_2012Metric
D12: P0D; D_SMA
D13: P1D; D_SMA
D14: USB-LED; LED_0603_1608Metric
F1: Polyfuse; FUSER_0ZCG0260BF2B
FB1: FerriteBead; BEADC2012X105N
H1, H2: MountingHole; MountingHole_3.2mm_M3
J1: Barrel_Jack; BarrelJack_Horizontal
J2: USB_C_Female_USB2_Small; USB_C_DB-108PWB
J3: SMS-CONN-0; S03BPASK2LFSN
J4: SMS-CONN-1; S03BPASK2LFSN
J5: ALS_CONN; CONN4_S04B-PASK_JST
J6: PUMP0-CONN; CONN2_S02B-PASK-2_JST
J7: PUMP1-CONN; CONN2_S02B-PASK-2_JST
J8: STEP-CONN; CONN4_S04B-PASK_JST
L1: L; IND_IFSC_1515AH_VIS
Q1: DMP6023LE-13; SOT-223
Q2, Q3: AO3400A; SOT-23
R1: 15k; R_0402_1005Metric
R2, R3: 100k; R_0402_1005Metric
R4, R5: 4.7K; R_0603_1608Metric
R6, R15, R16, R27: 1k; R_0402_1005Metric
R7, R30: 330; R_0402_1005Metric
R8: 47; R_0402_1005Metric
R10, R11: 5.1k; R_0603_1608Metric
R12, R13, R14: 4.7k; R_0402_1005Metric
R17, R18, R21, R23: 1k; R_0603_1608Metric
R19, R20, R22, R24: 10k; R_0603_1608Metric
R25, R26: 0.11; R_1206_3216Metric
R28: 1.5k; R_0402_1005Metric
R29, R31: 10k; R_0402_1005Metric
SW1: SW_RESET; SW_PUSH_6mm
SW2: SW_BOOT; SW_PUSH_6mm
TP1: TX; TestPoint_Pad_1.0x1.0mm
TP2: RX; TestPoint_Pad_1.0x1.0mm
TP3: TP_5V-U; TestPoint_Pad_1.0x1.0mm
TP4: TP_12V; TestPoint_Pad_1.0x1.0mm
TP5: TP_3V3; TestPoint_Pad_1.0x1.0mm
TP6: TP-5V-B; TestPoint_Pad_1.0x1.0mm
TP7: TP-GND; TestPoint_Pad_1.0x1.0mm
U1: ESP32-S3-WROOM-1; XCVR_ESP32-S3-WROOM-1-N16R2
U2: TPS5405DR; SOIC127P599X175-8N
U3, U4: ID_LM66100DCKR; SC-70-6
U5: ADS1115IDGS; TSSOP-10_3x3mm_P0.5mm
U6, U7: SI2301; TO-236_VIS
U8: TMC2209; QFN28_5X5_TRI
U9: TPD2E001DRLR; SOT50P160X60-5N
VR1: LM3940IMP-3.3_NOPB; VREG_LM3940IMP-3.3_NOPB

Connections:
1A: J8.2, U8.24 (OA1)
1B: J8.1, U8.26 (OB1)
2A: J8.3, U8.21 (OA2)
2B: J8.4, U8.1 (OB2)
5V-B: C6.1, C11.1, L1.2, TP6.1, U2.5 (VSENSE), U3.1 (VIN)
5V-U: C12.1, J2.A4 (VBUS), J2.A9 (VBUS), J2.B4 (VBUS), J2.B9 (VBUS), R28.1, TP3.1, U4.1 (VIN)
+3V3: C13.2, C14.2, C15.1, C16.1, C17.1, C18.1, C19.1, C20.1, C25.1, C26.1, C28.2, J5.1, R6.1, R12.2, R13.1, R14.1, R19.1, R20.1, R29.1, R31.1, TP5.1, U1.2 (3V3), U5.8 (VDD), U6.2 (S), U7.2 (S), U8.15 (VCC_IO), U9.1 (VCC), VR1.3 (OUT)
+5V: C7.2, C9.1, C10.2, C36.2, C37.2, D7.1 (VDD), U3.3 (*CE), U3.6 (VOUT), U4.3 (*CE), U4.6 (VOUT), VR1.1 (IN)
+12V: C2.2, C31.1, C32.1, C33.1, C34.2, C41.1, C42.1, C43.1, D12.1 (K), D13.1 (K), FB1.2, J6.1, J7.1, R5.1, TP4.1, U2.2 (VIN), U8.6 (VCP), U8.22 (VS), U8.28 (VS)
/ESP32-S3 Breakout/GPIO_14: R30.2, U1.22 (IO14)
/ESP32-S3 Breakout/GPIO_41: R8.1, U1.34 (IO41)
/ESP32-S3 Breakout/GPIO_42: R7.1, U1.35 (IO42)
ADC-RDY: R14.2, U1.19 (IO11), U5.2 (ALERT/RDY)
AOUT-0: J3.2, R16.1, U9.3 (IO1)
AOUT-1: J4.2, R15.1, U9.5 (IO2)
DIR: U1.6 (IO6), U8.19 (DIR)
EN: C35.1, R29.2, SW1.2, U1.3 (EN)
ENN: U1.9 (IO16), U8.2 (ENN)
GND: C1.2, C2.1, C4.2, C5.1, C6.2, C7.1, C9.2, C10.1, C11.2, C12.2, C13.1, C14.1, C15.2, C16.2, C17.2, C18.2, C19.2, C20.2, C21.2, C22.1, C23.2, C24.2, C25.2, C26.2, C27.2, C28.1, C30.2, C31.2, C32.2, C33.2, C34.1, C35.2, C36.1, C37.1, C41.2, C42.2, C43.2, D1.2 (A), D2.2 (A2), D4.1 (K), D5.1 (K), D6.1 (K), D7.3 (VSS), D8.1 (K), D9.1 (K), D14.1 (K), J1.2, J2.A1 (GND), J2.A12 (GND), J2.B1 (GND), J2.B12 (GND), J2.S1 (SHIELD), J3.3, J4.3, J5.4, Q2.3, Q3.3, R2.2, R3.1, R10.2, R11.2, R22.1, R24.1, R25.2, R26.2, SW1.1, SW2.1, TP7.1, U1.1 (GND), U1.40 (GND), U2.7 (GND), U3.2 (GND), U3.5 (ST), U4.2 (GND), U4.5 (ST), U5.1 (ADDR), U5.3 (GND), U8.3 (GND), U8.7 (SPREAD), U8.9 (MS1_AD0), U8.10 (MS2_AD1), U8.13 (CLK), U8.18 (GND), U8.29 (GND), U9.4 (GND), VR1.2 (GND_2), VR1.4 (GND_4)
GPIO_0: R31.2, SW2.2, U1.27 (IO0)
unnamed: C4.1, R1.2
unnamed: C3.1, D1.1 (K), L1.1, U2.8 (LX)
unnamed: D2.1 (A1), F1.2, Q1.2 (D), R4.2
unnamed: D3.2 (A), Q1.1 (G), R2.1
unnamed: C1.1, D3.1 (K), FB1.1, Q1.3 (S)
unnamed: D4.2 (A), R5.2
unnamed: D5.2 (A), R6.2
unnamed: D6.2 (A), R4.1
unnamed: D7.4 (DIN), R30.1
unnamed: D8.2 (A), R8.2
unnamed: D9.2 (A), R7.2
unnamed: D14.2 (A), R28.2
unnamed: F1.1, J1.1
unnamed: J2.A5 (CC1), R10.1
unnamed: J2.B5 (CC2), R11.1
unnamed: Q2.1, R21.2, R22.2
unnamed: Q3.1, R23.2, R24.2
unnamed: TP2.1, U1.36 (RXD0)
unnamed: TP1.1, U1.37 (TXD0)
unnamed: C3.2, U2.1 (BOOT)
unnamed: R1.1, U2.6 (COMP)
unnamed: R3.2, U2.3 (ROSC)
unnamed: C5.2, U2.4 (SS)
unnamed: C21.1, R16.2, U5.4 (AIN0)
unnamed: C22.2, R15.2, U5.5 (AIN1)
unnamed: R17.2, U6.1 (G)
unnamed: R18.2, U7.1 (G)
unnamed: C27.1, C30.1, U8.8 (5VOUT)
unnamed: R26.1, U8.23 (BRA)
unnamed: R25.1, U8.27 (BRB)
unnamed: C29.2, U8.5 (CPI)
unnamed: C29.1, U8.4 (CPO)
PGATE-0: R21.1, U1.10 (IO17)
PGATE-1: R23.1, U1.11 (IO18)
PUMP0-N: D12.2 (A), J6.2, Q2.2
PUMP1-N: D13.2 (A), J7.2, Q3.2
S3-RX: R27.1, U1.8 (IO15), U8.14 (PDN_UART)
S3-SCL: J5.2, R13.2, U1.38 (IO2), U5.10 (SCL)
S3-SDA: J5.3, R12.1, U1.39 (IO1), U5.9 (SDA)
S3-TX: R27.2, U1.7 (IO7)
SGATE-0: R17.1, R19.2, U1.21 (IO13)
SGATE-1: R18.1, R20.2, U1.20 (IO12)
STEP: U1.5 (IO5), U8.16 (STEP)
SVDD0: C23.1, J3.1, U6.3 (D)
SVDD1: C24.1, J4.1, U7.3 (D)
USB_D+: J2.A6 (D+), J2.B6 (D+), U1.14 (IO20)
USB_D-: J2.A7 (D-), J2.B7 (D-), U1.13 (IO19)
